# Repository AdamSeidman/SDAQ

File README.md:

# SDAQ
Stackable Data Acquisition System for RIT Baja.

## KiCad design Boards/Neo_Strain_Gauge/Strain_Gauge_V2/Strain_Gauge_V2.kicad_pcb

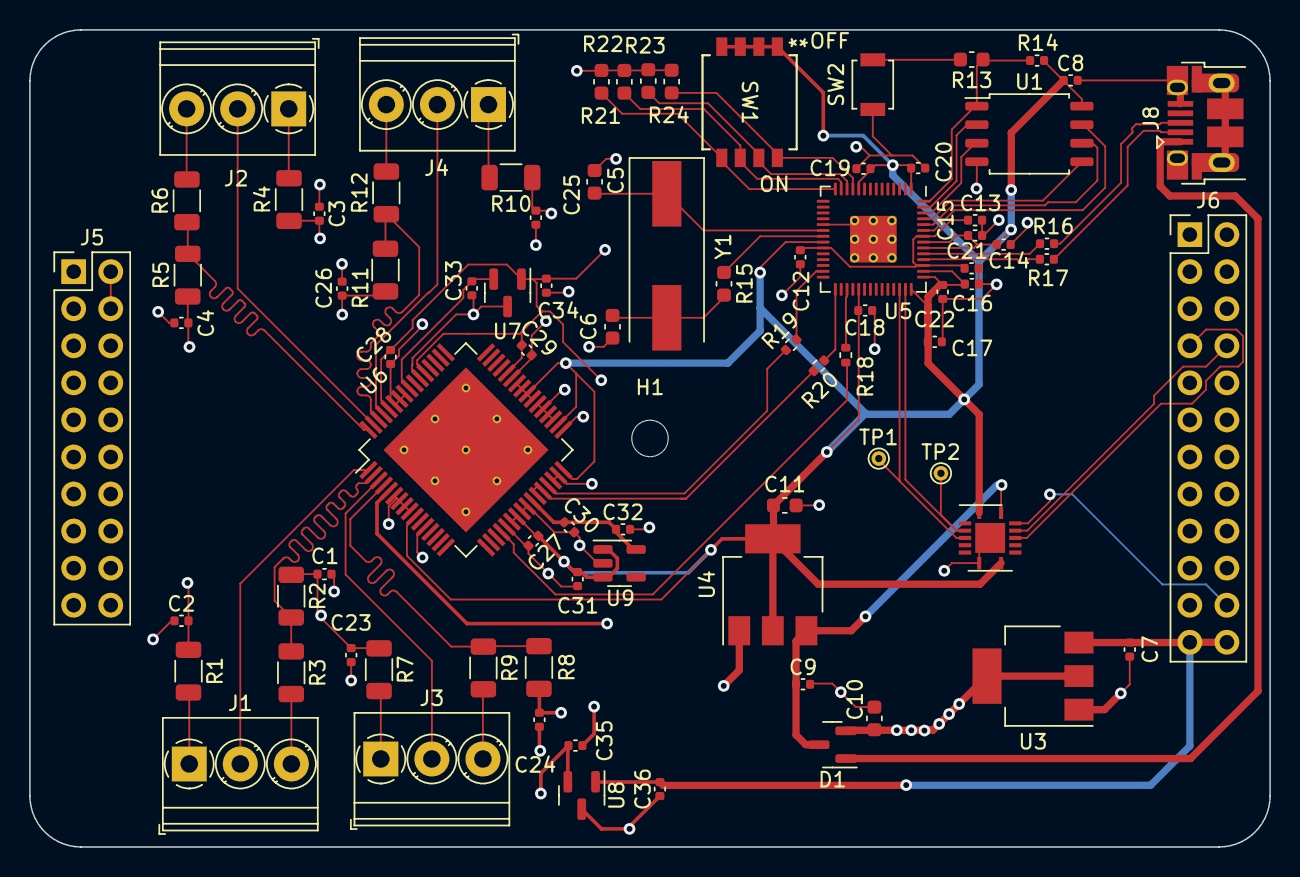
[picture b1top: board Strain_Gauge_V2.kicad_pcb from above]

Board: 4 copper layers, 85.0 x 56.0 mm, 83 parts (0 on the bottom side), 52 nets.

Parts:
C1, C2, C3, C4, C8, C12, C13, C14, C15, C16, C17, C18, C19, C20, C21, C22, C23, C24, C25, C26: 100n; C_0402_1005Metric
C5, C6: 27p; C_0603_1608Metric
C7, C9, C27, C28, C29, C30, C31, C32, C33, C34, C35, C36: 10u; C_0402_1005Metric
C10, C11: 22u; C_0603_1608Metric
D1: BAT54C; SOT-23
H1: MountingHole; MountingHole_2.5mm
J1, J2, J3, J4: Screw_Terminal_01x03; TerminalBlock_Phoenix_PT-1,5-3-3.5-H_1x03_P3.50mm_Horizontal
J5: Conn_02x10_Counter_Clockwise; PinHeader_2x10_P2.54mm_Vertical
J6: Conn_02x12_Counter_Clockwise; PinHeader_2x12_P2.54mm_Vertical
J8: USB_B_Micro; USB_Micro-B_Amphenol_10103594-0001LF_Horizontal_modified
R1, R4, R7, R10: 350; R_1206_3216Metric
R2, R3, R5, R6, R8, R9, R11, R12: 1000; R_1206_3216Metric
R13, R15, R21, R22, R23, R24: 1k; C_0603_1608Metric
R14: DNF; C_0402_1005Metric
R16, R17: 27; C_0402_1005Metric
R18, R19, R20: 50; R_0402_1005Metric
SW1: SW_DIP_x04; SW4_1571983_4P_TEC
SW2: SW_Push; SW_SPST_B3U-1000P
TP1, TP2: TestPoint; TestPoint_THTPad_D1.0mm_Drill0.5mm
U1: W25Q128JVS; SOIC-8_5.23x5.23mm_P1.27mm
U2: TXS0104ERGYR; Texas_S-PVQFN-N14
U3: AZ1117-5.0; SOT-223-3_TabPin2
U4: NCP1117-3.3_SOT223; SOT-223-3_TabPin2
U5: RP2040; RP2040-QFN-56
U6: ADS1274IPAPR; PowerPad
U7: MAX6102; SOT-23
U8: MAX6105; SOT-23
U9: AP2112K-1.8; SOT-23-5
Y1: ABLS-12.000MHZ-B4-T; Crystal_SMD_HC49-SD

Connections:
+1V1: C12.1, C13.1, C14.1, U5.23 (DVDD), U5.45 (VREG_VOUT), U5.50 (DVDD)
+1V8: C30.1, C32.1, U6.26 (DVDD), U9.5 (VOUT)
+3V3: C8.1, C11.1, C15.1, C16.1, C17.1, C18.1, C19.1, C20.1, C21.1, C22.1, C27.1, C31.1, R14.1, SW1.1, SW1.2, SW1.3, SW1.4, U1.8 (VCC), U2.1 (VCCA), U2.8 (OE), U4.2 (VO), U5.1 (IOVDD), U5.10 (IOVDD), U5.22 (IOVDD), U5.33 (IOVDD), U5.42 (IOVDD), U5.43 (ADC_AVDD), U5.44 (VREG_IN), U5.48 (USB_VDD), U5.49 (IOVDD), U6.10 (CLKDIV), U6.22 (IOVDD), U6.23 (IOVDD), U6.32 (FORMAT0), U6.34 (MODE0), U6.39 (*PWDN4), U6.40 (*PWDN3), U6.41 (*PWDN2), U6.42 (*PWDN1), U9.1 (VIN), U9.3 (EN)
+5V: C10.1, C28.1, C29.1, C34.2, D1.2, U3.2 (VO), U6.5 (AVDD), U6.44 (AVDD), U6.53 (AVDD), U6.60 (AVDD), U7.1 (IN)
+5VA: C1.2, C2.2, C3.2, C4.2, C23.2, C24.2, C25.2, C26.2, C35.1, R1.1, R2.1, R4.1, R5.1, R7.1, R8.1, R10.1, R11.1, U8.2 (OUT)
+12V: C7.1, C36.2, J6.23, J6.24, U3.3 (VI), U8.1 (IN)
/Analog Reader/IN0+: J3.2, U6.3 (AINP1)
/Analog Reader/IN0-: R8.2, R9.1, U6.4 (AINN1)
/Analog Reader/IN1+: J1.2, U6.1 (AINP2)
/Analog Reader/IN1-: R2.2, R3.1, U6.2 (AINN2)
/Analog Reader/IN2+: J2.2, U6.63 (AINP3)
/Analog Reader/IN2-: R5.2, R6.1, U6.64 (AINN3)
/Analog Reader/IN3+: J4.2, U6.61 (AINP4)
/Analog Reader/IN3-: R11.2, R12.1, U6.62 (AINN4)
/Analog Reader/INT_SPI_CLK: R20.2, U6.27 (CLK), U6.28 (SCLK)
/Analog Reader/Wheatstone1/TERM-: J1.1, R1.2
/Analog Reader/Wheatstone2/TERM-: J2.1, R4.2
/Analog Reader/Wheatstone3/TERM-: J3.1, R7.2
/Analog Reader/Wheatstone/TERM-: J4.1, R10.2
/DRDY: R19.1, U5.27 (GPIO16)
/MISO: R18.1, U5.31 (GPIO20)
/REG_POWER: C9.1, D1.3, U2.14 (VCCB), U4.3 (VI)
/Raspberry Pi/GPIO8: R24.2, SW1.8, U5.11 (GPIO8)
/Raspberry Pi/GPIO9: R23.2, SW1.7, U5.12 (GPIO9)
/Raspberry Pi/GPIO10: R22.2, SW1.6, U5.13 (GPIO10)
/Raspberry Pi/GPIO11: R21.2, SW1.5, U5.14 (GPIO11)
/Raspberry Pi/GPIO28_ADC2: TP1.1, U2.4 (A3), U5.40 (GPIO28_ADC2)
/Raspberry Pi/GPIO29_ADC3: TP2.1, U2.3 (A2), U5.41 (GPIO29_ADC3)
/Raspberry Pi/QSPI_SCLK: U1.6 (CLK), U5.52 (QSPI_SCLK)
/Raspberry Pi/QSPI_SD0: U1.5 (DI(IO0)), U5.53 (QSPI_SD0)
/Raspberry Pi/QSPI_SD1: U1.2 (DO(IO1)), U5.55 (QSPI_SD1)
/Raspberry Pi/QSPI_SD2: U1.3 (IO2), U5.54 (QSPI_SD2)
/Raspberry Pi/QSPI_SD3: U1.7 (IO3), U5.51 (QSPI_SD3)
/Raspberry Pi/QSPI_SS: R13.1, R14.2, U1.1 (~CS), U5.56 (QSPI_SS)
/Raspberry Pi/USB_DR+: R16.2, U5.47 (USB_DP)
/Raspberry Pi/USB_DR-: R17.2, U5.46 (USB_DM)
/Raspberry Pi/XIN: C5.1, U5.20 (XIN), Y1.1
/Raspberry Pi/XOUT: R15.1, U5.21 (XOUT)
/Raspberry Pi/~USB_BOOT: R13.2, SW2.2
/SPI_CLK: R20.1, U5.29 (GPIO18)
/USB_D+: J8.3 (D+), R16.1
/USB_D-: J8.2 (D-), R17.1
/VBUS: D1.1, J8.1 (VBUS)
/reset: J6.22, U2.13 (B1)
/rpi_5v: J5.2, J5.4
/scl: J6.8, U2.12 (B2)
/sda: J6.7, U2.11 (B3)
GND: C1.1, C2.1, C3.1, C4.1, C5.2, C6.2, C7.2, C8.2, C9.2, C10.2, C11.2, C12.2, C13.2, C14.2, C15.2, C16.2, C17.2, C18.2, C19.2, C20.2, C21.2, C22.2, C23.1, C24.1, C25.1, C26.1, C27.2, C28.2, C29.2, C30.2, C31.2, C32.2, C33.2, C34.1, C35.2, C36.1, J1.3, J2.3, J3.3, J4.3, J5.6, J5.9, J5.14, J5.20, J6.5, J6.10, J6.14, J6.19, J8.5 (GND), J8.6 (Shield), R3.2, R6.2, R9.2, R12.2, R21.1, R22.1, R23.1, R24.1, SW2.1, U1.4 (GND), U2.7 (GND), U2.15 (Pad), U3.1 (GND), U4.1 (GND), U5.19 (TESTEN), U5.57 (GND), U6.6 (AGND), U6.7 (DGND), U6.8 (TEST0), U6.9 (TEST1), U6.12 (DIN), U6.21 (DGND), U6.24 (DGND), U6.25 (DGND), U6.30 (FORMAT2), U6.31 (FORMAT1), U6.33 (MODE1), U6.35 (*PWDN8), U6.36 (*PWDN7), U6.37 (*PWDN6), U6.38 (*PWDN5), U6.43 (AGND), U6.54 (AGND), U6.57 (VREFN), U6.58 (AGND), U6.59 (AGND), U6.65 (EPAD), U7.3 (GND), U8.3 (GND), U9.2 (GND)
unnamed: C6.1, R15.2, Y1.2
unnamed: R19.2, U6.29 (*DRDY/FSYNC)
unnamed: R18.2, U6.20 (DOUT1)
unnamed: C33.1, U6.56 (VREFP), U7.2 (OUT)

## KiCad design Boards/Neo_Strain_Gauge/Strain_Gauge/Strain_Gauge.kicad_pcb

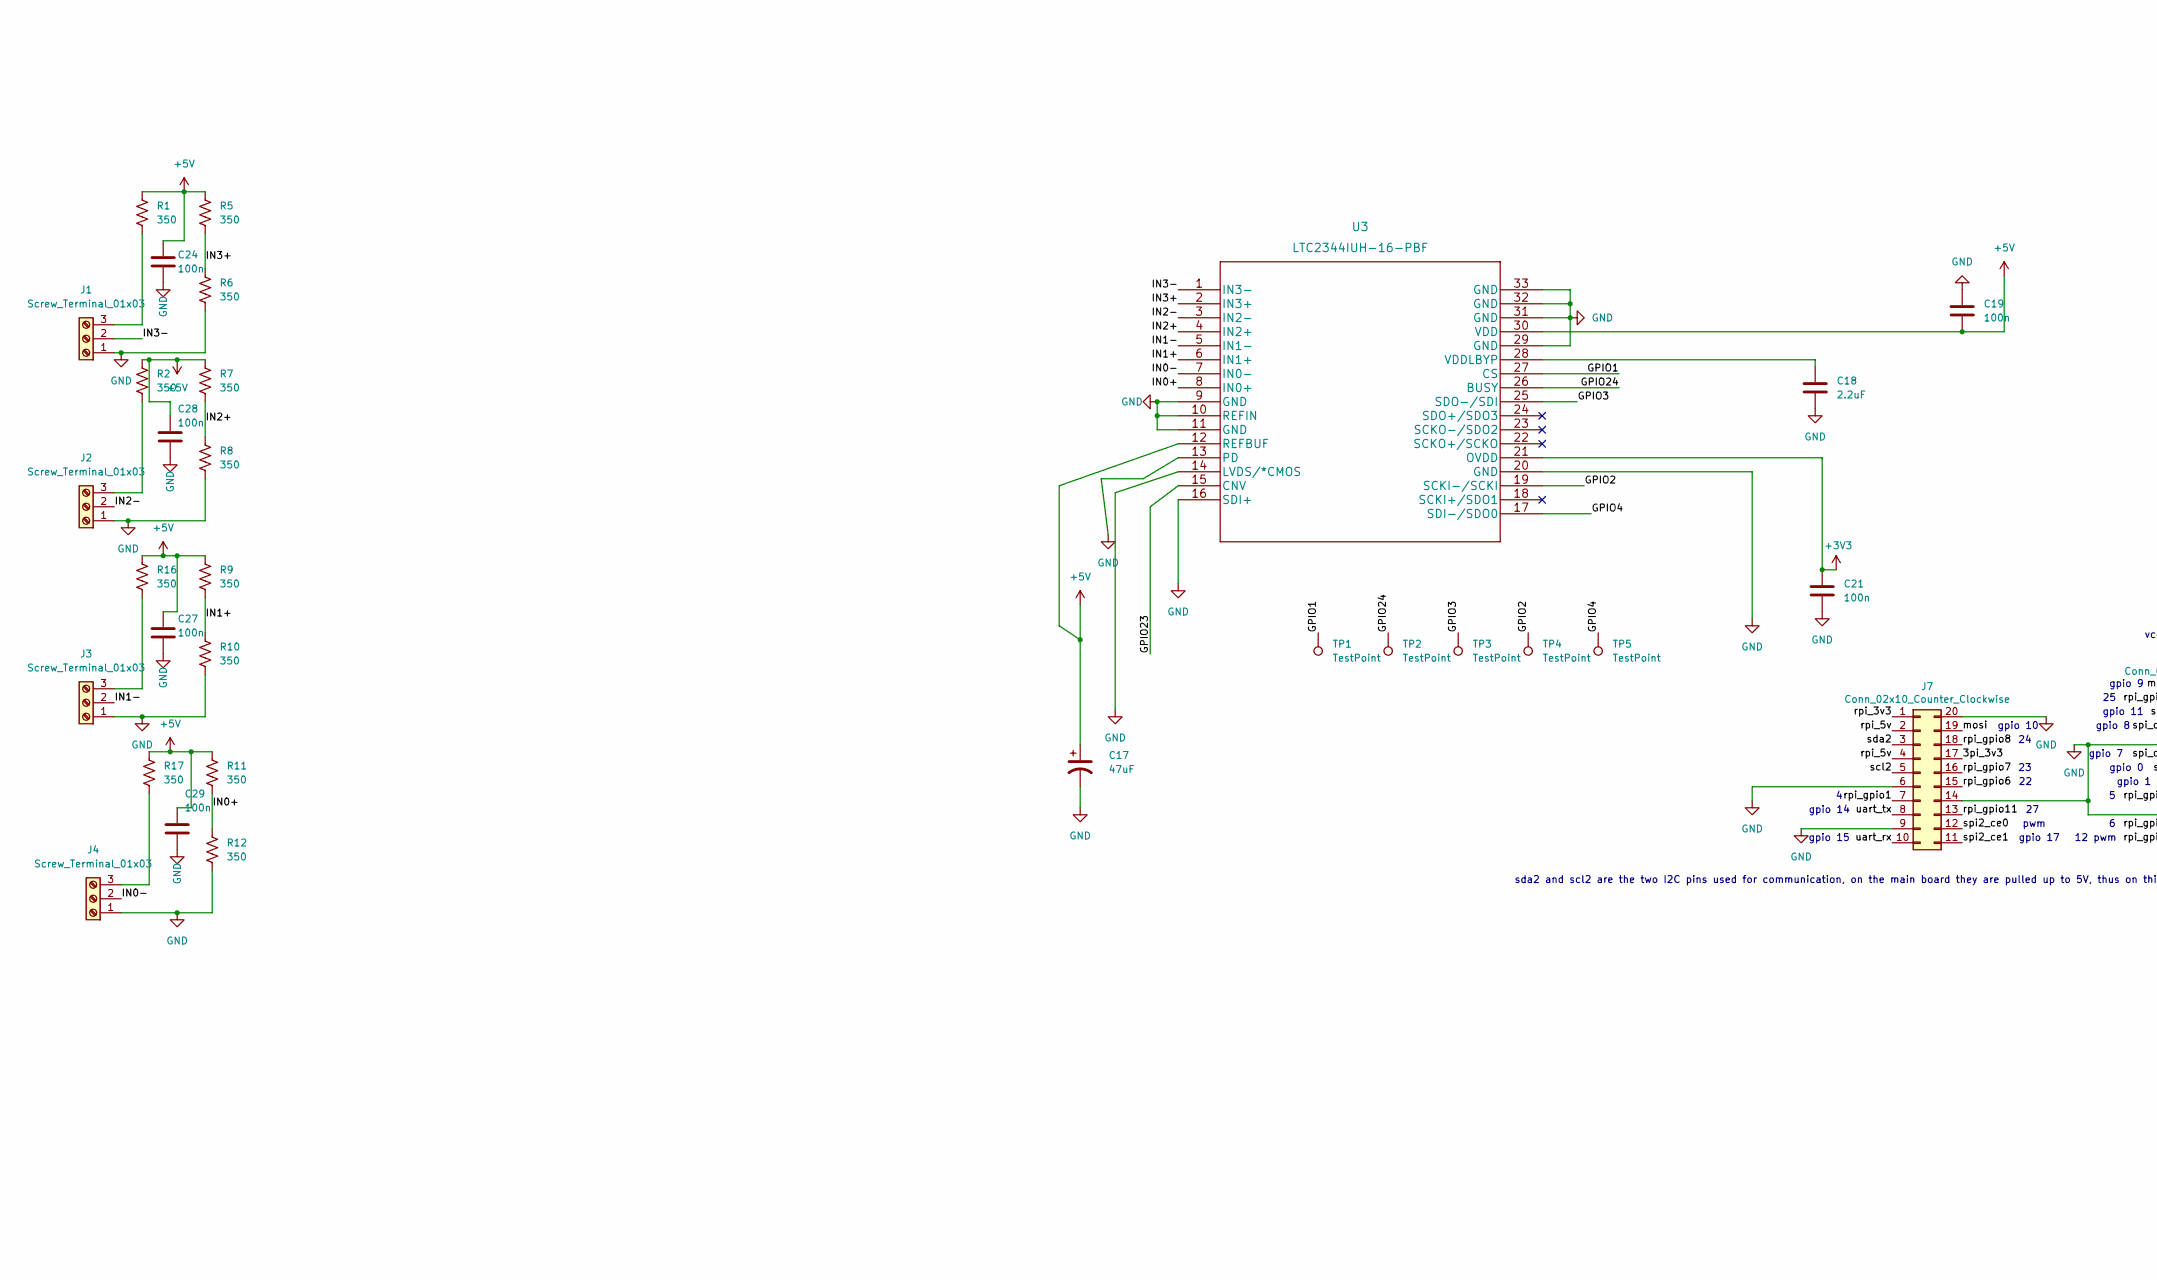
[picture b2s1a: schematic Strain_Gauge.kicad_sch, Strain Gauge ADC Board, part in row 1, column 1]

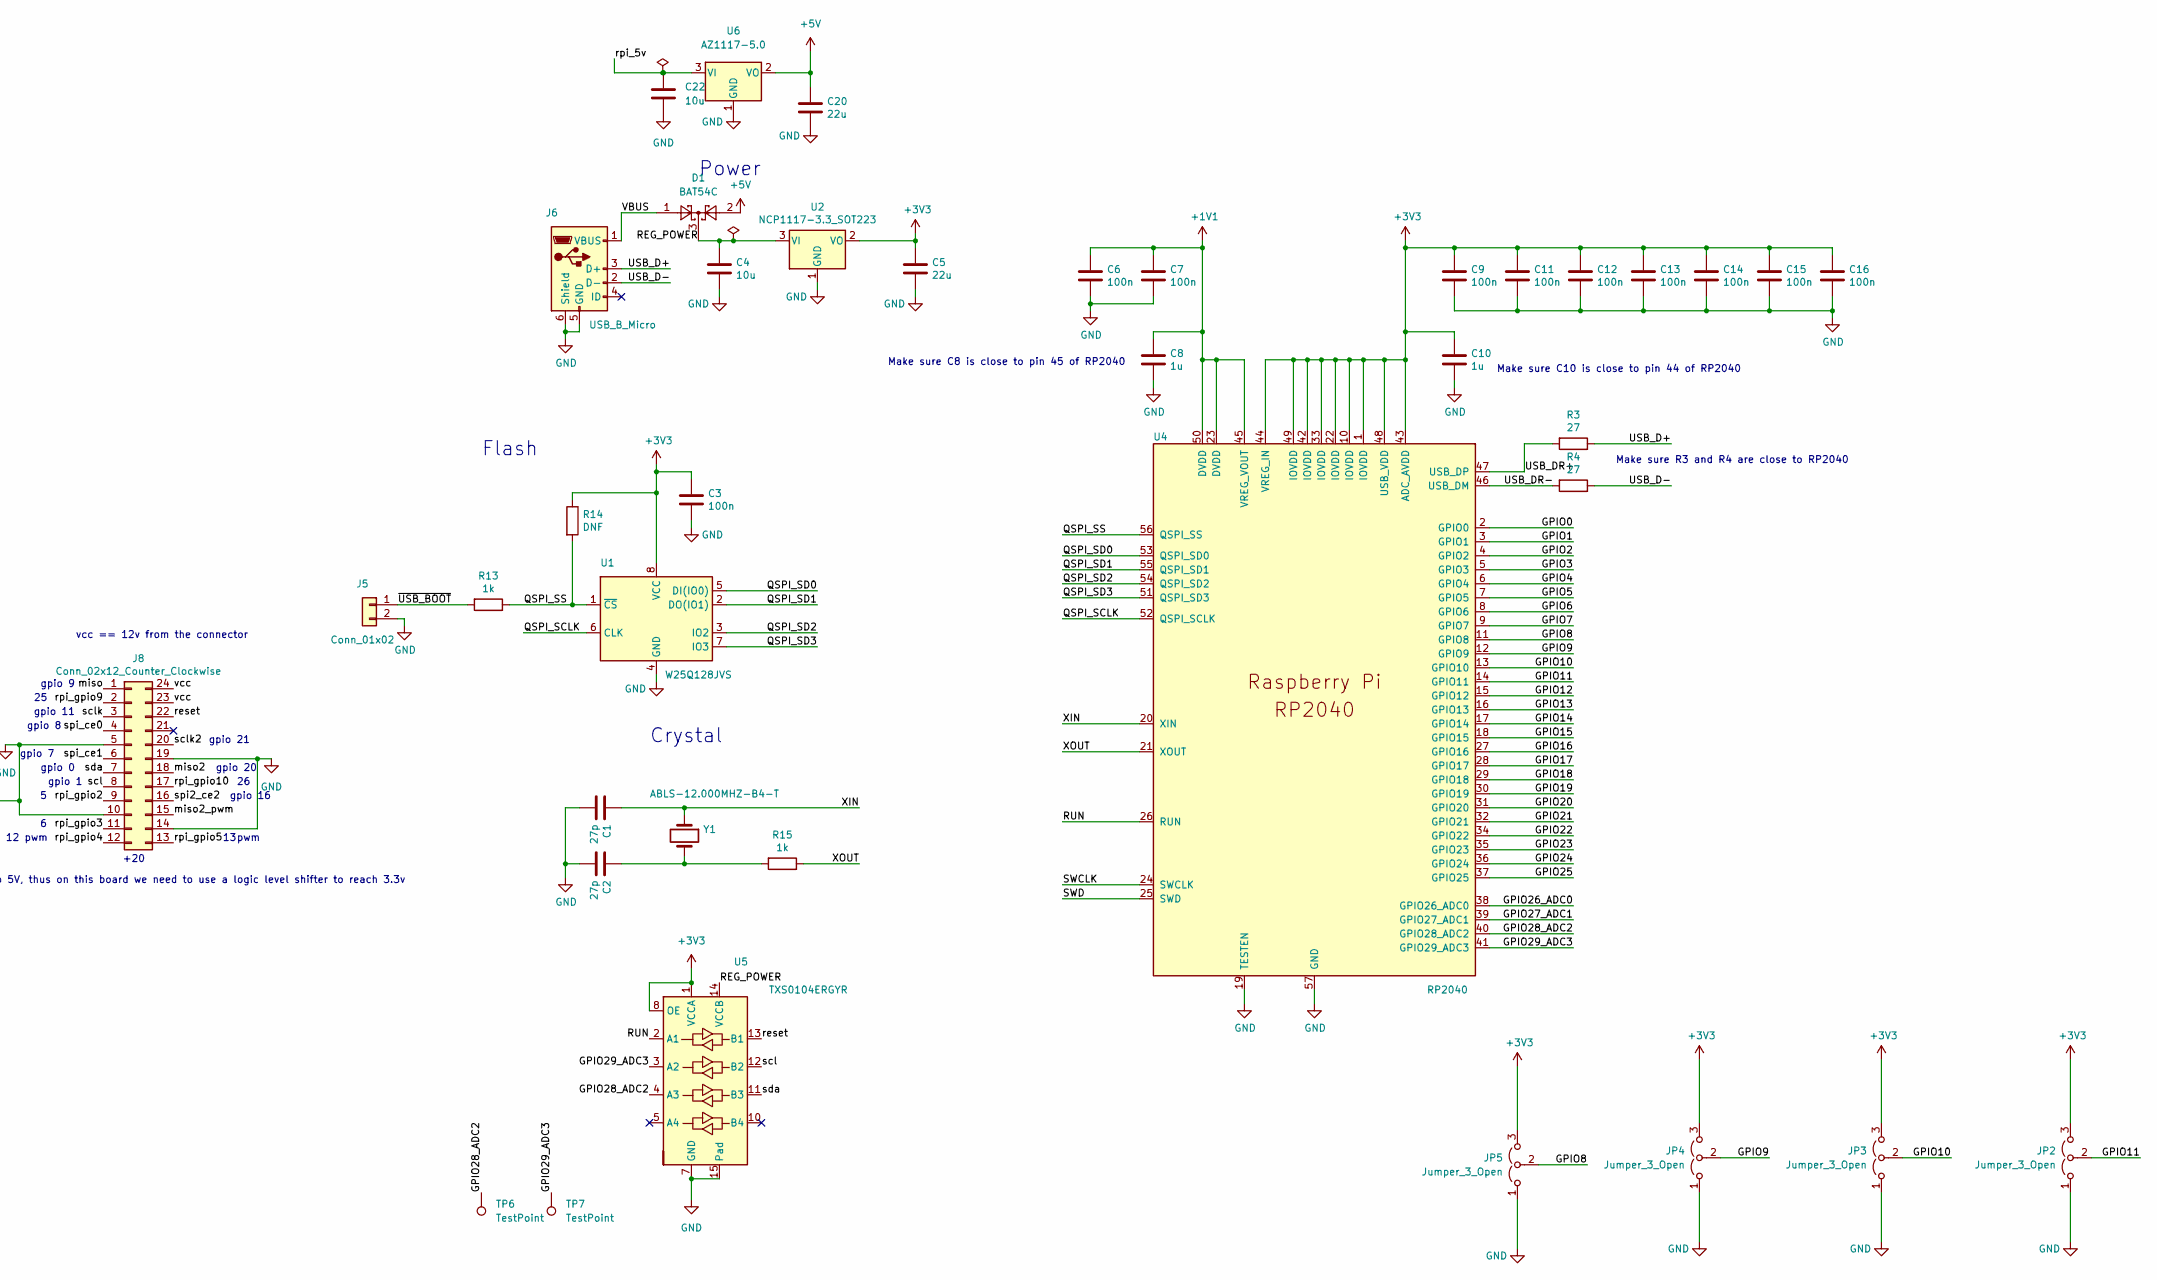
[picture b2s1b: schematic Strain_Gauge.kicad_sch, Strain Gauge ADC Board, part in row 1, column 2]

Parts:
C1, C2: 27p; C_0603_1608Metric
C3, C6, C7, C9, C11, C12, C13, C14, C15, C16, C19, C21, C24, C27, C28, C29: 100n; C_0402_1005Metric
C4, C22: 10u; C_0603_1608Metric
C5, C20: 22u; C_0603_1608Metric
C8, C10: 1u; C_0402_1005Metric
C17: 47uF; CP_EIA-3216-18_Kemet-A
C18: 2.2uF; C_0603_1608Metric
D1: BAT54C; SOT-23
J1, J2, J3, J4: Screw_Terminal_01x03; TerminalBlock_Phoenix_PT-1,5-3-3.5-H_1x03_P3.50mm_Horizontal
J5: Conn_01x02; PinHeader_1x02_P2.54mm_Vertical
J6: USB_B_Micro; USB_Micro-B_Amphenol_10103594-0001LF_Horizontal_modified
J7: Conn_02x10_Counter_Clockwise; PinHeader_2x10_P2.54mm_Vertical
J8: Conn_02x12_Counter_Clockwise; PinHeader_2x12_P2.54mm_Vertical
JP2, JP3, JP4, JP5: Jumper_3_Open; PinHeader_1x03_P2.54mm_Vertical
R1, R5, R6, R7, R8, R9, R10, R11, R12, R16, R17: 350; R_1206_3216Metric
R2: 350; R_1210_3225Metric
R3, R4: 27; C_0402_1005Metric
R13, R15: 1k; C_0603_1608Metric
R14: DNF; C_0402_1005Metric
TP1, TP2, TP3, TP4, TP5, TP6, TP7: TestPoint; TestPoint_THTPad_D1.0mm_Drill0.5mm
U1: W25Q128JVS; SOIC-8_5.23x5.23mm_P1.27mm
U2: NCP1117-3.3_SOT223; SOT-223-3_TabPin2
U3: LTC2344IUH-16-PBF; QFN-32-1EP_5x5mm_P0.5mm_EP3.45x3.45mm
U4: RP2040; RP2040-QFN-56
U5: TXS0104ERGYR; Texas_S-PVQFN-N14
U6: AZ1117-5.0; SOT-223-3_TabPin2
Y1: ABLS-12.000MHZ-B4-T; Crystal_SMD_HC49-SD

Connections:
+1V1: C6.1, C7.1, C8.1, U4.23 (DVDD), U4.45 (VREG_VOUT), U4.50 (DVDD)
+3V3: C3.1, C5.1, C9.1, C10.1, C11.1, C12.1, C13.1, C14.1, C15.1, C16.1, C21.1, JP2.3 (B), JP3.3 (B), JP4.3 (B), JP5.3 (B), R14.1, U1.8 (VCC), U2.2 (VO), U3.21 (OVDD), U4.1 (IOVDD), U4.10 (IOVDD), U4.22 (IOVDD), U4.33 (IOVDD), U4.42 (IOVDD), U4.43 (ADC_AVDD), U4.44 (VREG_IN), U4.48 (USB_VDD), U4.49 (IOVDD), U5.1 (VCCA), U5.8 (OE)
+5V: C17.1, C19.2, C20.1, C24.2, C27.2, C28.2, C29.2, D1.2, R1.1, R2.1, R5.1, R7.1, R9.1, R11.1, R16.1, R17.1, U3.12 (REFBUF), U3.30 (VDD), U6.2 (VO)
/3pi_3v3: J7.17
/GPIO0: U4.2 (GPIO0)
/GPIO1: TP1.1, U3.27 (CS), U4.3 (GPIO1)
/GPIO2: TP4.1, U3.19 (SCKI-/SCKI), U4.4 (GPIO2)
/GPIO3: TP3.1, U3.25 (SDO-/SDI), U4.5 (GPIO3)
/GPIO4: TP5.1, U3.17 (SDI-/SDO0), U4.6 (GPIO4)
/GPIO5: U4.7 (GPIO5)
/GPIO6: U4.8 (GPIO6)
/GPIO7: U4.9 (GPIO7)
/GPIO8: JP5.2 (C), U4.11 (GPIO8)
/GPIO9: JP4.2 (C), U4.12 (GPIO9)
/GPIO10: JP3.2 (C), U4.13 (GPIO10)
/GPIO11: JP2.2 (C), U4.14 (GPIO11)
/GPIO12: U4.15 (GPIO12)
/GPIO13: U4.16 (GPIO13)
/GPIO14: U4.17 (GPIO14)
/GPIO15: U4.18 (GPIO15)
/GPIO16: U4.27 (GPIO16)
/GPIO17: U4.28 (GPIO17)
/GPIO18: U4.29 (GPIO18)
/GPIO19: U4.30 (GPIO19)
/GPIO20: U4.31 (GPIO20)
/GPIO21: U4.32 (GPIO21)
/GPIO22: U4.34 (GPIO22)
/GPIO23: U3.15 (CNV), U4.35 (GPIO23)
/GPIO24: TP2.1, U3.26 (BUSY), U4.36 (GPIO24)
/GPIO25: U4.37 (GPIO25)
/GPIO26_ADC0: U4.38 (GPIO26_ADC0)
/GPIO27_ADC1: U4.39 (GPIO27_ADC1)
/GPIO28_ADC2: TP6.1, U4.40 (GPIO28_ADC2), U5.4 (A3)
/GPIO29_ADC3: TP7.1, U4.41 (GPIO29_ADC3), U5.3 (A2)
/IN0+: R11.2, R12.1, U3.8 (IN0+)
/IN0-: J4.2, U3.7 (IN0-)
/IN1+: R9.2, R10.1, U3.6 (IN1+)
/IN1-: J3.2, U3.5 (IN1-)
/IN2+: R7.2, R8.1, U3.4 (IN2+)
/IN2-: J2.2, U3.3 (IN2-)
/IN3+: R5.2, R6.1, U3.2 (IN3+)
/IN3-: J1.2, U3.1 (IN3-)
/QSPI_SCLK: U1.6 (CLK), U4.52 (QSPI_SCLK)
/QSPI_SD0: U1.5 (DI(IO0)), U4.53 (QSPI_SD0)
/QSPI_SD1: U1.2 (DO(IO1)), U4.55 (QSPI_SD1)
/QSPI_SD2: U1.3 (IO2), U4.54 (QSPI_SD2)
/QSPI_SD3: U1.7 (IO3), U4.51 (QSPI_SD3)
/QSPI_SS: R13.1, R14.2, U1.1 (~CS), U4.56 (QSPI_SS)
/REG_POWER: C4.1, D1.3, U2.3 (VI), U5.14 (VCCB)
/RUN: U4.26 (RUN), U5.2 (A1)
/SWCLK: U4.24 (SWCLK)
/SWD: U4.25 (SWD)
/USB_D+: J6.3 (D+), R3.1
/USB_D-: J6.2 (D-), R4.1
/USB_DR+: R3.2, U4.47 (USB_DP)
/USB_DR-: R4.2, U4.46 (USB_DM)
/VBUS: D1.1, J6.1 (VBUS)
/XIN: C1.1, U4.20 (XIN), Y1.1
/XOUT: R15.1, U4.21 (XOUT)
/miso: J8.1
/miso2: J8.18
/miso2_pwm: J8.15
/mosi: J7.19
/reset: J8.22, U5.13 (B1)
/rpi_3v3: J7.1
/rpi_5v: C22.1, J7.2, J7.4, U6.3 (VI)
/rpi_gpio1: J7.7
/rpi_gpio2: J8.9
/rpi_gpio3: J8.11
/rpi_gpio4: J8.12
/rpi_gpio5: J8.13
/rpi_gpio6: J7.15
/rpi_gpio7: J7.16
/rpi_gpio8: J7.18
/rpi_gpio9: J8.2
/rpi_gpio10: J8.17
/rpi_gpio11: J7.13
/scl: J8.8, U5.12 (B2)
/scl2: J7.5
/sclk: J8.3
/sclk2: J8.20
/sda: J8.7, U5.11 (B3)
/sda2: J7.3
/spi2_ce0: J7.12
/spi2_ce1: J7.11
/spi2_ce2: J8.16
/spi_ce0: J8.4
/spi_ce1: J8.6
/uart_rx: J7.10
/uart_tx: J7.8
/vcc: J8.23, J8.24
/~USB_BOOT: J5.1, R13.2
GND: C1.2, C2.2, C3.2, C4.2, C5.2, C6.2, C7.2, C8.2, C9.2, C10.2, C11.2, C12.2, C13.2, C14.2, C15.2, C16.2, C17.2, C18.2, C19.1, C20.2, C21.2, C22.2, C24.1, C27.1, C28.1, C29.1, J1.1, J2.1, J3.1, J4.1, J5.2, J6.5 (GND), J6.6 (Shield), J7.6, J7.9, J7.14, J7.20, J8.5, J8.10, J8.14, J8.19, JP2.1 (A), JP3.1 (A), JP4.1 (A), JP5.1 (A), R6.2, R8.2, R10.2, R12.2, U1.4 (GND), U2.1 (GND), U3.9 (GND), U3.10 (REFIN), U3.11 (GND), U3.13 (PD), U3.14 (LVDS/*CMOS), U3.16 (SDI+), U3.20 (GND), U3.29 (GND), U3.31 (GND), U3.32 (GND), U3.33 (GND), U4.19 (TESTEN), U4.57 (GND), U5.7 (GND), U5.15 (Pad), U6.1 (GND)
unnamed: C2.1, R15.2, Y1.2
unnamed: J1.3, R1.2
unnamed: J2.3, R2.2
unnamed: J3.3, R16.2
unnamed: J4.3, R17.2
unnamed: C18.1, U3.28 (VDDLBYP)

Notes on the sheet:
gpio 16
gpio 9
Make sure C8 is close to pin 45 of RP2040
gpio 8
Make sure C10 is close to pin 44 of RP2040
gpio 7
Crystal
Make sure R3 and R4 are close to RP2040
gpio 17
gpio 11
vcc == 12v from the connector
gpio 0
gpio 20
+20
sda2 and scl2 are the two I2C pins used for communication, on the main board they are pulled up to 5V, thus on this board we need to use a logic level shifter to reach 3.3v
12 pwm
gpio 21
gpio 10
Power
gpio 14
pwm
Flash
gpio 1
gpio 15

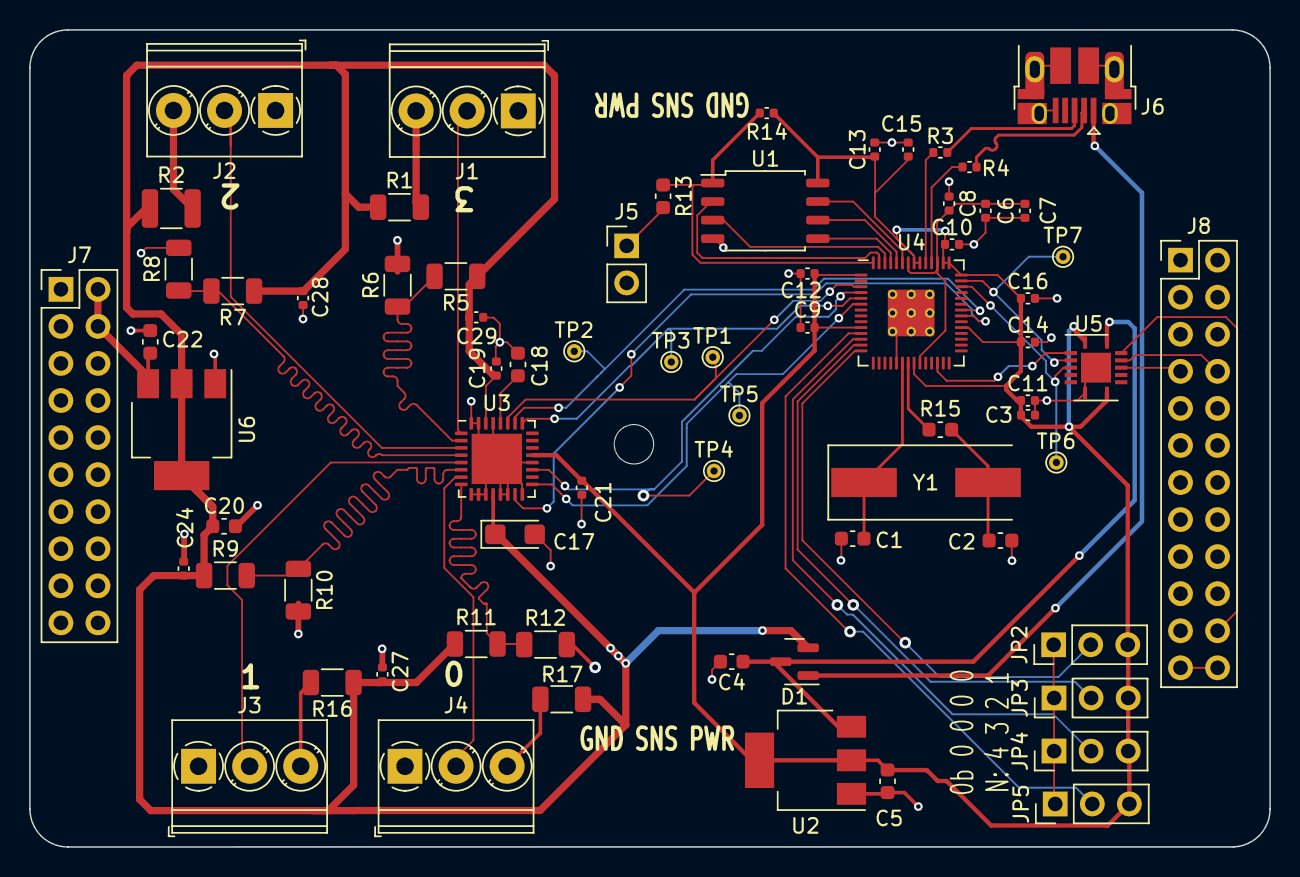
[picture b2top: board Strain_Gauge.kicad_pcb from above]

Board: 2 copper layers, 85.0 x 56.0 mm, 70 parts (0 on the bottom side), 51 nets.

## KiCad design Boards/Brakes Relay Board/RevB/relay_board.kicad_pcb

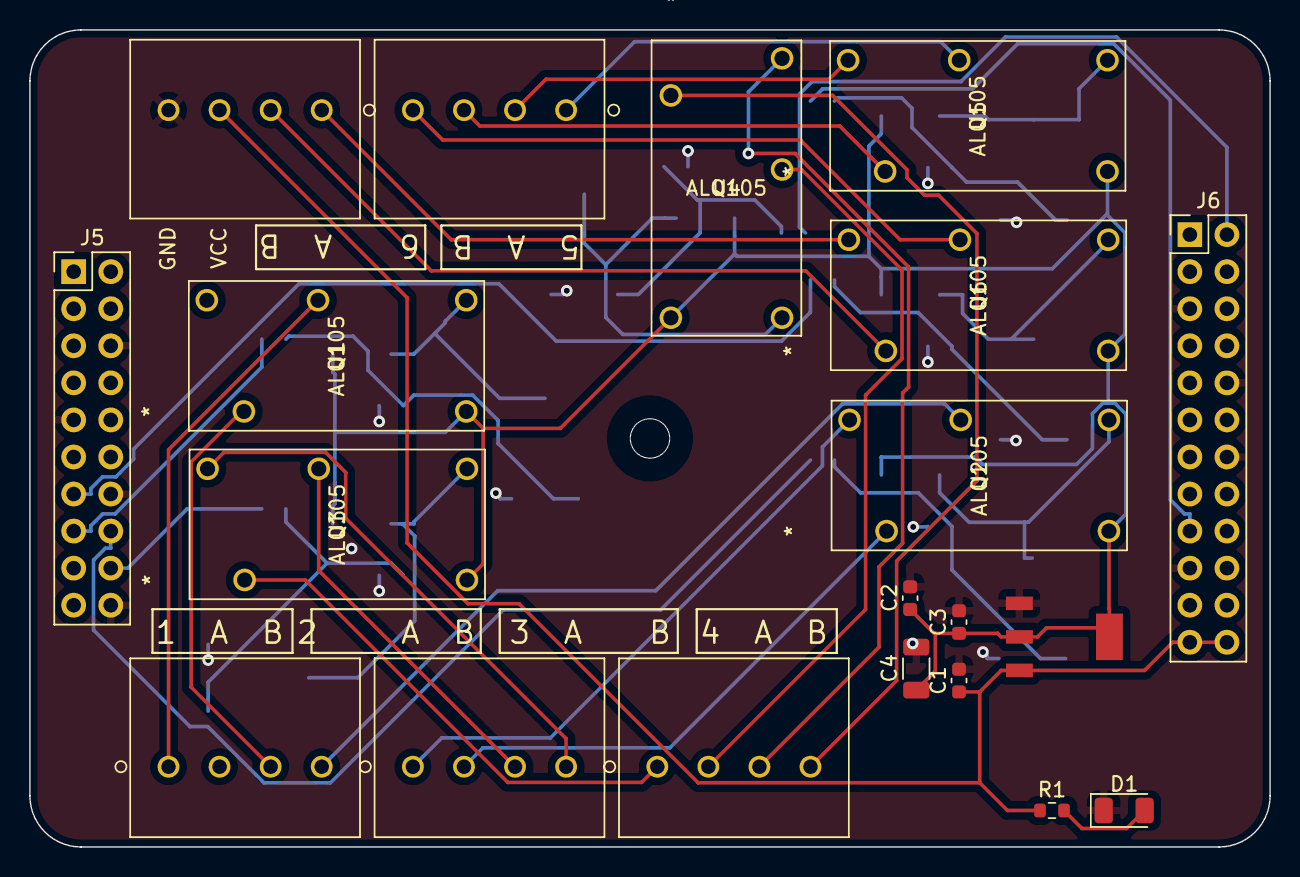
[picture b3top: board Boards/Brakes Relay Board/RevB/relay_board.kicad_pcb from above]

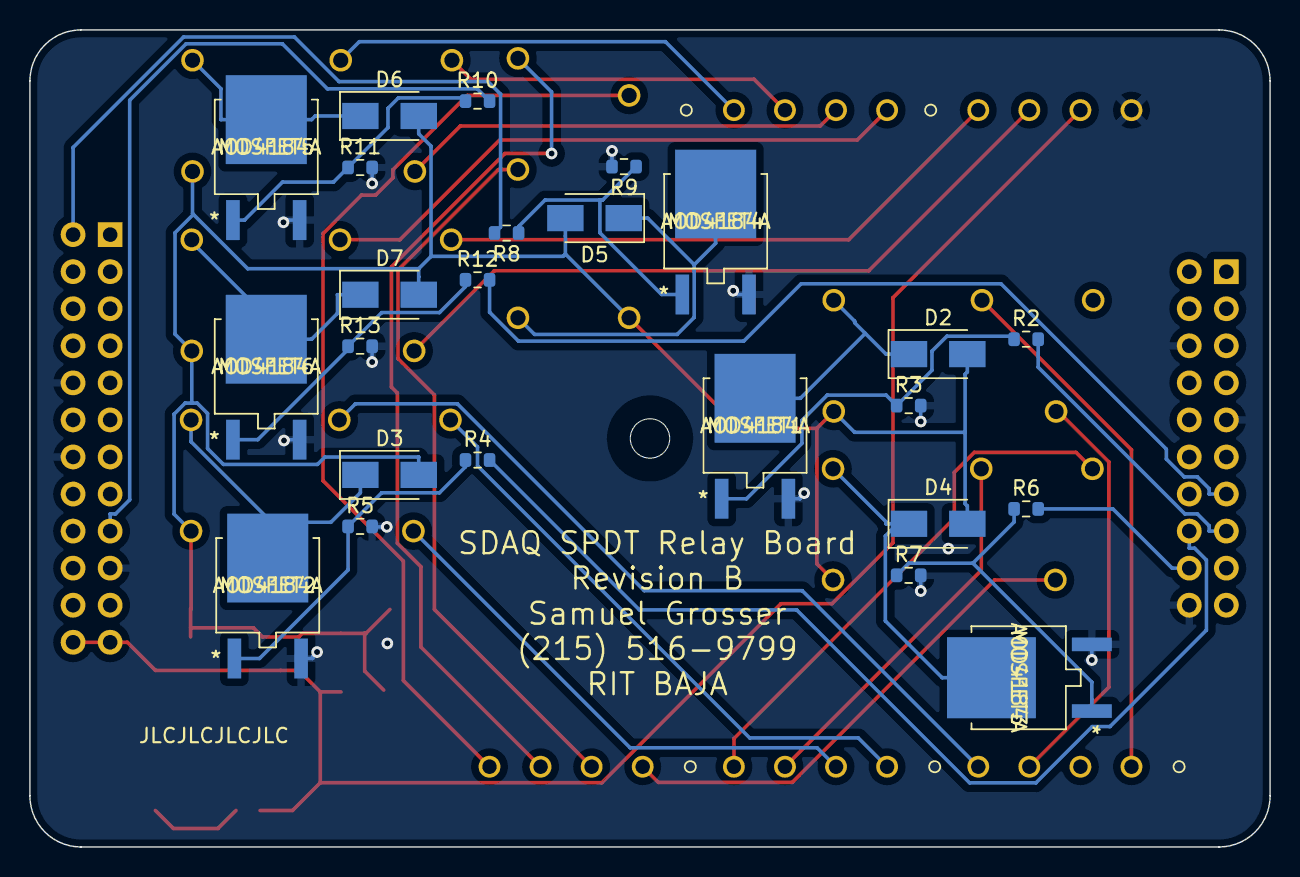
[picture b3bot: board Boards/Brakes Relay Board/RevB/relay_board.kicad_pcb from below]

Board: 2 copper layers, 85.0 x 56.0 mm, 44 parts (24 on the bottom side), 39 nets.

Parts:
C1, C2, C3: C_0603_1608Metric
C4: C_1206_3216Metric
D1: LED; D_1206_3216Metric
D2, D3, D4, D5, D6, D7: DIODE; D_SMA
J1, J2, J3, J4, J7: Screw_Terminal_01x04; 1984989
J5: Conn_02x10_Counter_Clockwise; PinHeader_2x10_P2.54mm_Vertical
J6: Conn_02x12_Counter_Clockwise; PinHeader_2x12_P2.54mm_Vertical
MOSFET1, MOSFET2, MOSFET3, MOSFET4, MOSFET5, MOSFET6: AOD4184A
R1: 1800; R_0603_1608Metric
R2, R4, R6, R8, R10, R12: 100; R_0603_1608Metric
R3, R5, R7, R9, R11, R13: 100k; R_0603_1608Metric
U1, U2, U3, U4, U5, U6: ALQ105
VR1: SOT230P700X180-4N

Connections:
+5V: C2.1, C3.1, C4.1, D2.2 (A), D3.2 (A), D4.2 (A), D5.2 (A), D6.2 (A), D7.2 (A), U1.4, U2.4, U3.4, U4.4, U5.4, U6.4, VR1.2 (VOUT2), VR1.4 (VOUT)
/Ch1: J1.1, U1.2
/Ch1B: J1.3, U1.5
/Ch2: J1.4, U2.2
/Ch2A: J2.1, U2.1
/Ch2B: J2.2, U2.5
/Ch3: J2.3, U3.2
/Ch3A: J2.4, U3.1
/Ch3B: J3.1, U3.5
/Ch4: J3.2, U4.2
/Ch4A: J3.3, U4.1
/Ch4B: J3.4, U4.5
/Ch5: J4.1, U5.2
/Ch5A: J4.2, U5.1
/Ch5B: J4.3, U5.5
/Ch6: J4.4, U6.2
/Ch6A: J7.1, U6.1
/Ch6B: J7.2, U6.5
/R0: J5.15, R2.2
/R1: J5.16, R4.2
/R2: J5.18, R6.2
/R3: J6.2, R8.2
/R4: J6.17, R10.2
/R5: J5.13, R12.2
/VCC: C1.1, J6.23, J6.24, J7.3, R1.1, VR1.3 (VIN)
GNDREF: C1.2, C2.2, C3.2, C4.2, D1.1 (K), J5.6, J5.9, J5.14, J5.20, J6.5, J6.10, J6.14, J6.19, J7.4, MOSFET1.3, MOSFET2.3, MOSFET3.3, MOSFET4.3, MOSFET5.3, MOSFET6.3, R3.2, R5.2, R7.2, R9.2, R11.2, R13.2, VR1.1 (ADJ/GND)
unnamed: D1.2 (A), R1.2
unnamed: D2.1 (K), MOSFET1.2, U1.3
unnamed: D3.1 (K), MOSFET2.2, U2.3
unnamed: D4.1 (K), MOSFET3.2, U3.3
unnamed: D5.1 (K), MOSFET4.2, U4.3
unnamed: D6.1 (K), MOSFET5.2, U5.3
unnamed: D7.1 (K), MOSFET6.2, U6.3
unnamed: MOSFET1.1, R2.1, R3.1
unnamed: MOSFET2.1, R4.1, R5.1
unnamed: MOSFET3.1, R6.1, R7.1
unnamed: MOSFET4.1, R8.1, R9.1
unnamed: MOSFET5.1, R10.1, R11.1
unnamed: MOSFET6.1, R12.1, R13.1

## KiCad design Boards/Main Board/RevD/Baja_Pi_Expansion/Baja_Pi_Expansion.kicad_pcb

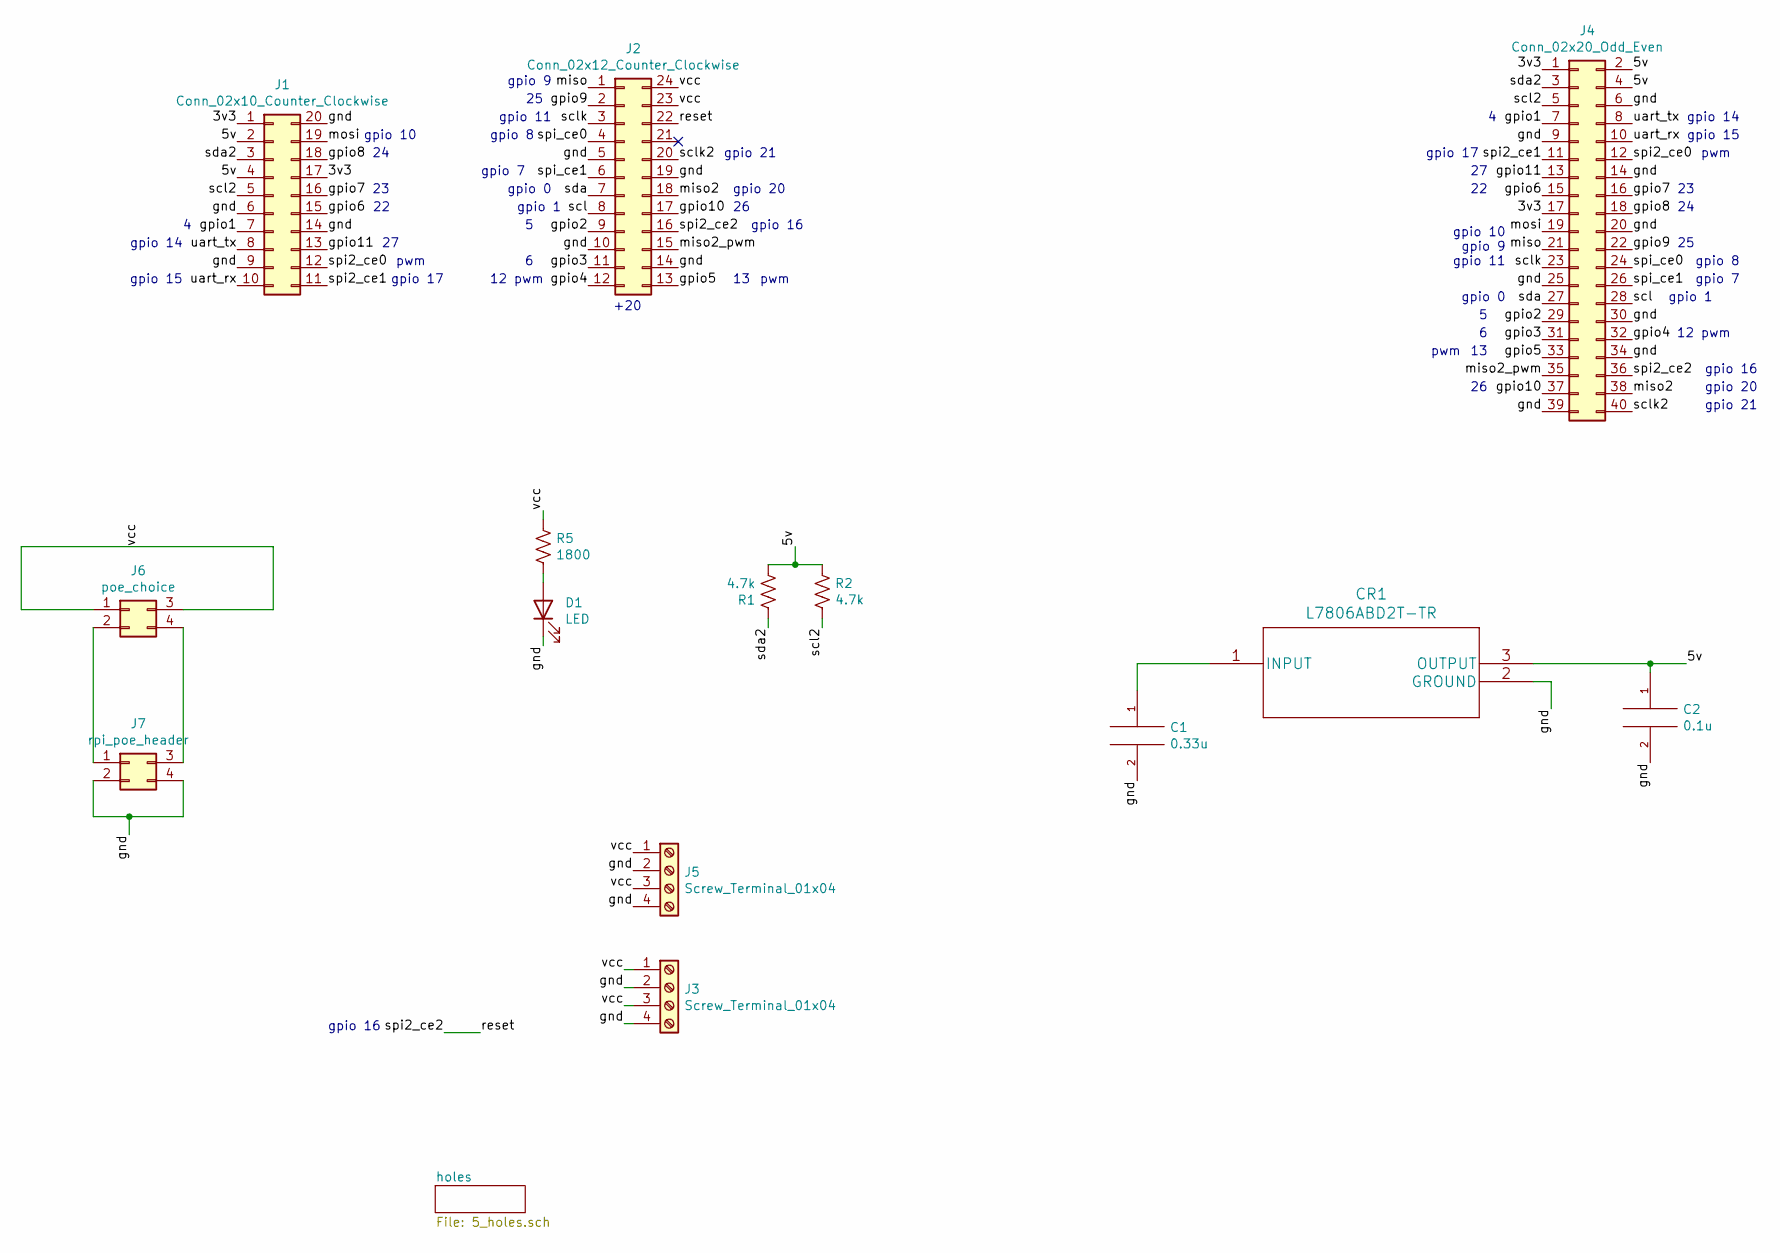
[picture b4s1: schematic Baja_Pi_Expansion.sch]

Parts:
C1: 0.33u; C_0603_1608Metric
C2: 0.1u; C_0603_1608Metric
CR1: L7806ABD2T-TR
D1: LED; D_1206_3216Metric
J1: Conn_02x10_Counter_Clockwise; PinHeader_2x10_P2.54mm_Vertical
J2: Conn_02x12_Counter_Clockwise; PinHeader_2x12_P2.54mm_Vertical
J3, J5: Screw_Terminal_01x04; Spring_4
J4: Conn_02x20_Odd_Even; PinHeader_2x20_P2.54mm_Vertical
J6: poe_choice; PinHeader_2x02_P2.54mm_Vertical
J7: rpi_poe_header; PinHeader_2x02_P2.54mm_Vertical
R1, R2: 4.7k; R_0603_1608Metric
R5: 1800; R_0603_1608Metric

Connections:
/3v3: J1.1, J1.17, J4.1, J4.17
/5v: C2.1, CR1.3 (OUTPUT), J1.2, J1.4, J4.2, J4.4, R1.1, R2.2
/gnd: C1.2, C2.2, CR1.2 (GROUND), D1.1 (K), J1.6, J1.9, J1.14, J1.20, J2.5, J2.10, J2.14, J2.19, J3.2, J3.4, J4.6, J4.9, J4.14, J4.20, J4.25, J4.30, J4.34, J4.39, J5.2, J5.4, J7.2, J7.4
/gpio1: J1.7, J4.7
/gpio2: J2.9, J4.29
/gpio3: J2.11, J4.31
/gpio4: J2.12, J4.32
/gpio5: J2.13, J4.33
/gpio6: J1.15, J4.15
/gpio7: J1.16, J4.16
/gpio8: J1.18, J4.18
/gpio9: J2.2, J4.22
/gpio10: J2.17, J4.37
/gpio11: J1.13, J4.13
/miso: J2.1, J4.21
/miso2: J2.18, J4.38
/miso2_pwm: J2.15, J4.35
/mosi: J1.19, J4.19
/reset: J2.16, J2.22, J4.36
/scl: J2.8, J4.28
/scl2: J1.5, J4.5, R2.1
/sclk: J2.3, J4.23
/sclk2: J2.20, J4.40
/sda: J2.7, J4.27
/sda2: J1.3, J4.3, R1.2
/spi2_ce0: J1.12, J4.12
/spi2_ce1: J1.11, J4.11
/spi_ce0: J2.4, J4.24
/spi_ce1: J2.6, J4.26
/uart_rx: J1.10, J4.10
/uart_tx: J1.8, J4.8
/vcc: J2.23, J2.24, J3.1, J3.3, J5.1, J5.3, J6.1, J6.3, R5.1
unnamed: C1.1, CR1.1 (INPUT)
unnamed: D1.2 (A), R5.2
unnamed: J6.2, J7.1
unnamed: J6.4, J7.3

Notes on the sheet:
pwm
gpio 14
gpio 15
gpio 17
gpio 8
gpio 7
gpio 1
12 pwm
gpio 16
gpio 20
gpio 21
gpio 10 gpio 9 gpio 11
gpio 0
gpio 11
gpio 10
gpio 9
+20

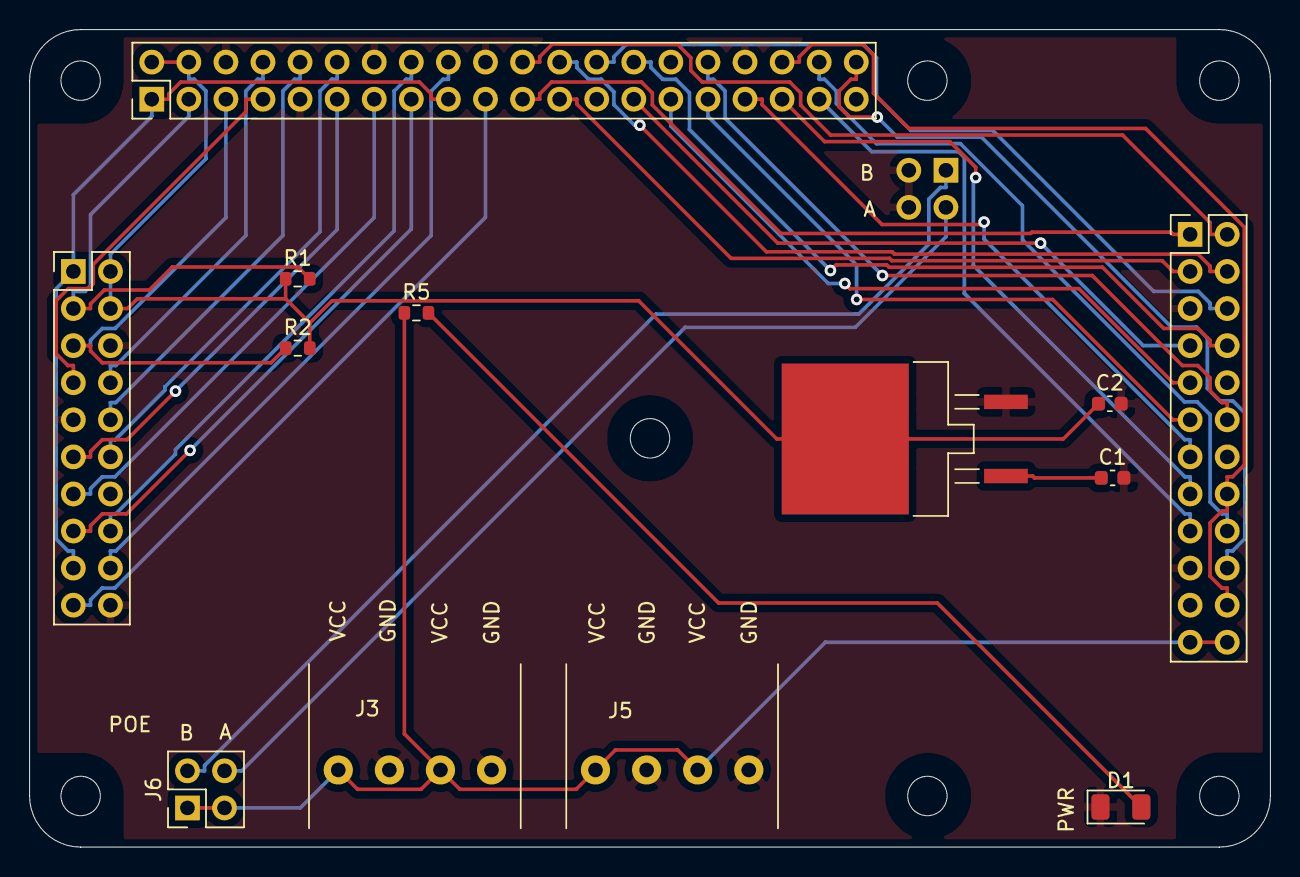
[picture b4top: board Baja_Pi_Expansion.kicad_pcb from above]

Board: 2 copper layers, 85.0 x 56.0 mm, 21 parts (1 on the bottom side), 36 nets.

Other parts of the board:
H1: MH1; MountingHole_2.7mm_M2.5
H2: MH2; MountingHole_2.7mm_M2.5
H3: MH3; MountingHole_2.7mm_M2.5
H4, H6: MH4; MountingHole_2.7mm_M2.5
H5, H7: MH_c; MountingHole_2.7mm_M2.5

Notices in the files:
parts and their libraries:
Copyright 2021 Accelerated Designs. All rights reserved.
